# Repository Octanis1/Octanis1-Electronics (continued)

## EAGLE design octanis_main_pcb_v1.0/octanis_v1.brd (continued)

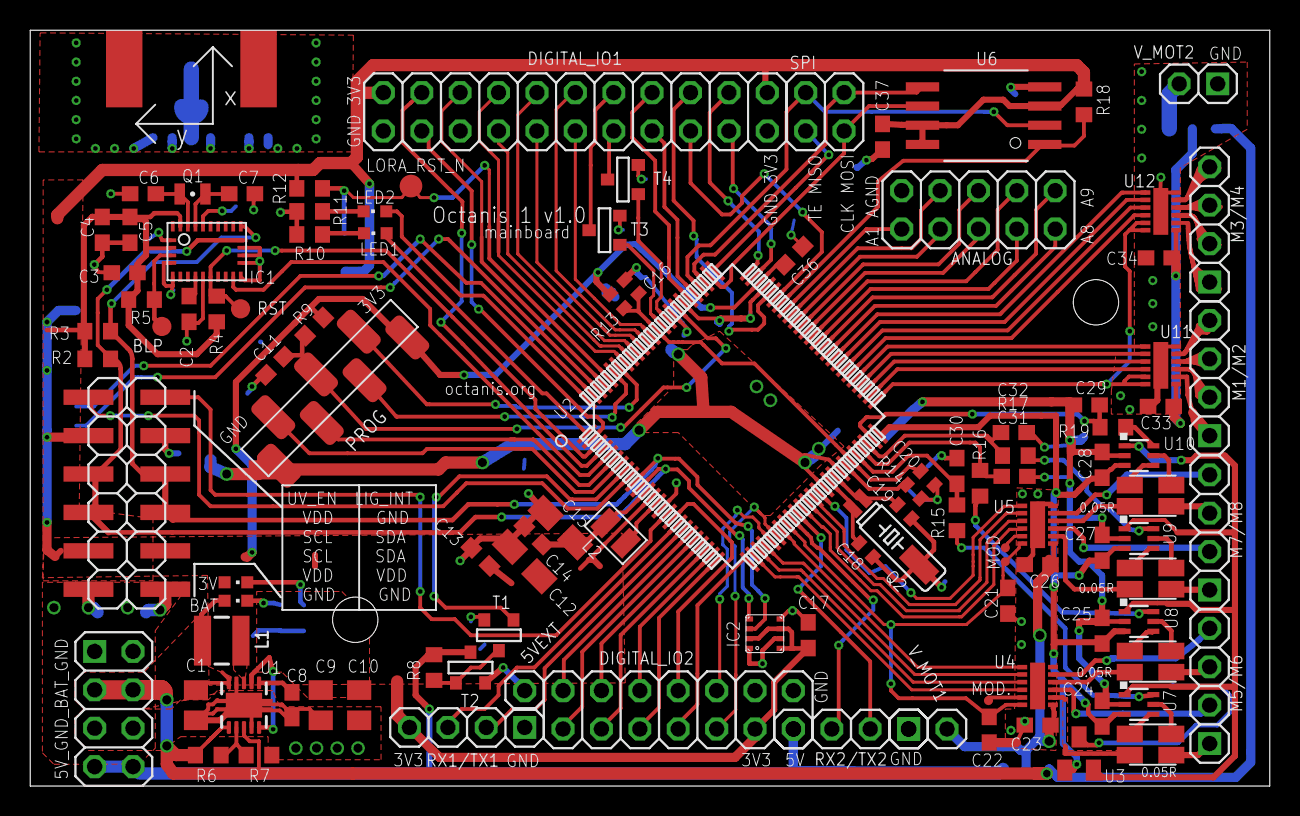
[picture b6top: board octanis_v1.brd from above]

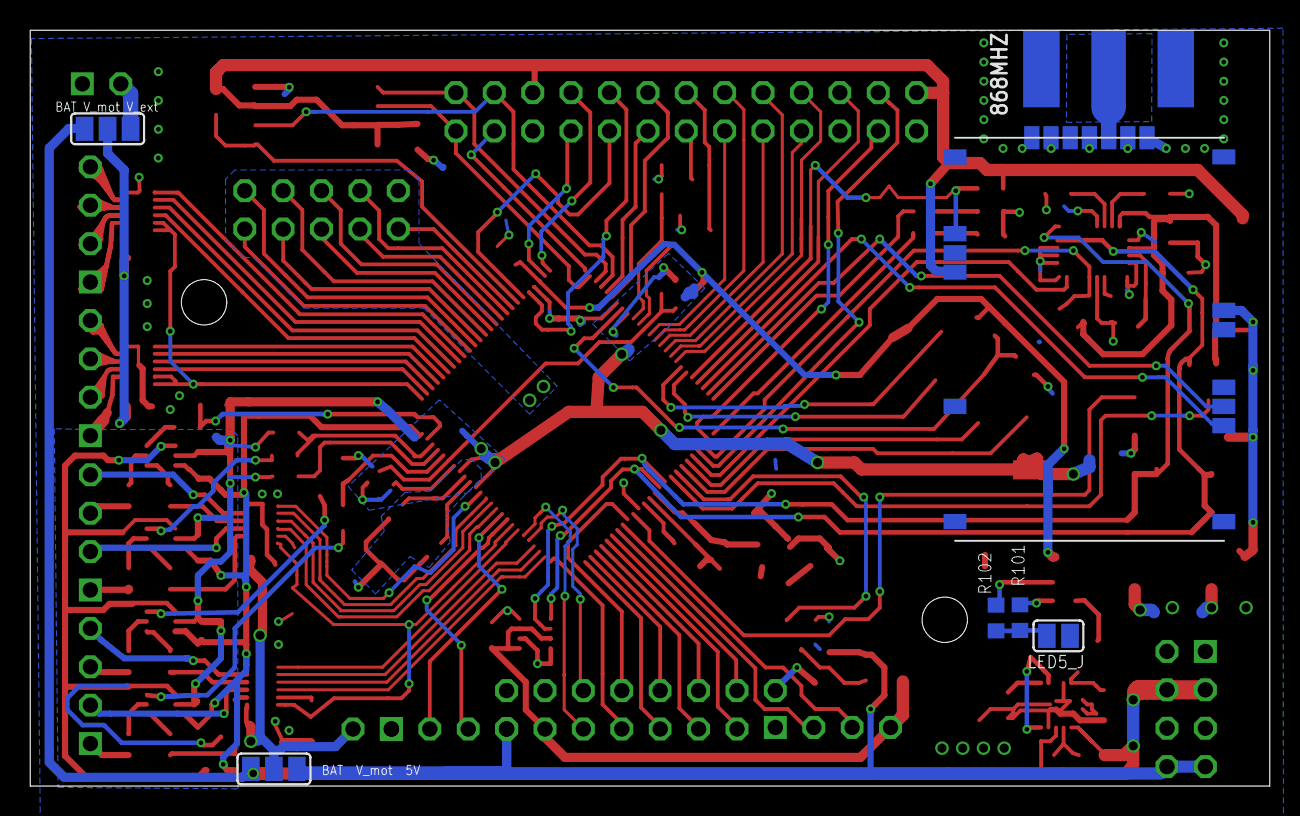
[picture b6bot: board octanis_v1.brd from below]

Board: 2 copper layers, 82.0 x 50.0 mm, 117 parts (7 on the bottom side), 151 nets.

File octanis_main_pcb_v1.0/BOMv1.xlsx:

Part | list exported from / | Users/raffael/Deskto | p/Octanis/Octanis1-El | ectronics/octa | nis_main_pcb_v1.0/octanis_v1.sch at | 42442.656944444447
Qty | Value | Device | Package | Parts |  | Description MF MPN OC_FARNELL OC_NEWARK PACKAGE SUPPLIER TP_SIGNAL_NAME URL VAL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
1 | 142-0701-801 | SMACONNECTOR_EDGE | SMA_EDGELAUNCH | 868MHZ |  | SMA Connector
4 | 0.05R | CURRENT_RESISTOR | 4PADS_RESISTOR | RS1, RS2, RS3, | RS4
1 | 0R | R-EU_R0402 | R0402 | R13 |  | RESISTOR, European symbol
3 | 100k | R-EU_R0603 | R0603 | R4, R5, R12 |  | RESISTOR, European symbol
2 | 100n | C-EUC0402 | C0402 | C16, C20 |  | CAPACITOR, European symbol
8 | 100n | C-EUC0603 | C0603 | C2, C3, C8, C1 | 3, C14, C17, C36, C37 | CAPACITOR, European symbol
1 | 100k | R-EU_R0603 | R0603 | R18 |  | RESISTOR, European symbol
4 | 10n | C-EUC0603 | C0603 | C24, C25, C27, | C28 | CAPACITOR, European symbol
3 | 10u | C-EUC0805K | C0805K | C1, C9, C10 |  | CAPACITOR, European symbol
2 | 10u | CPOL-EUA/3216-18R | A/3216-18R | C12, C15 |  | POLARIZED CAPACITOR, European symbol
2 | 120n | C-EUC0603 | C0603 | C4, C5 |  | CAPACITOR, European symbol
2 | 12p | C-EUC0402 | C0402 | C18, C19 |  | CAPACITOR, European symbol
2 | 12p | C-EUC0603 | C0603 | C6, C7 |  | CAPACITOR, European symbol
3 | 1M | R-EU_R0603 | R0603 | R6, R7, R8 |  | RESISTOR, European symbol
3 | 1k | R-EU_R0603 | R0603 | R10, R11, R102 |  | RESISTOR, European symbol
1 | 1n | C-EUC0603 | C0603 | C11 |  | CAPACITOR, European symbol
3 | 2N7002P,215 | NMOSSOT23 | SOT-23 | T1, T3, T4 |  | MOS FET unknown unknown
1 | 1.2k | R-EU_R0603 | R0603 | R101 |  | RESISTOR, European symbol
1 | ST2012SB32768H5 | FC-12M | FC-12M | Q1 |  | kHz RANGE CRYSTAL UNIT http://www.mouser.ch/ProductDetail/ECS/ECS-327-125-12-TR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
1 | AB26TRQ-32.768kHz-T | MS3V-T1R | MS3V-T1R | Q2
1 | HT-193UYG-5592 | LEDCHIPLED_0603 | CHIPLED_0603 | 3V |  | LED green
2 | 4.7k | R-EU_R0603 | R0603 | R2, R3 |  | RESISTOR, European symbol
1 | 4.7uH | LQM2MP_G0 | 806 | L2
10 | 470n | C-EUC0603 | C0603 | C21, C22, C23, | C26, C29, C30, C31, C32, C33, C34 | CAPACITOR, European symbol
1 | 47k | R-EU_R0603 | R0603 | R9 |  | RESISTOR, European symbol
4 | 6.8k | R-EU_R0603 | R0603 | R15, R16, R17, | R19 | RESISTOR, European symbol
1 | 91k 0.1% ±25 ppm/°C | R-EU_R0402 | R0402 | R14 |  | RESISTOR, European symbol
1 | HT-193UYG-5592 | LEDCHIPLED_0603 | CHIPLED_0603 | BAT |  | LED green
1 | BME280 | BME280 | BME280 | IC2 |  | DIGITAL HUMIDITY, PRESSURE AND TEMPERATURE SENSOR* Digital interface I²C (up to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
1 | BNO055A | BNO055A | BNO055 | IC1
1 | BNO055_COORDINATES | BNO055_COORDINATES | BNO055_COORDINATES | U$3
1 | DMP2066LSN | PMOSSOT23 | SOT-23 | T2 |  | MOS FET unknown unknown
2 | DRV8835DSSR | DRV8836DSSR | SON50P200X300X80-13N | U4, U5 |  | DUAL LOW VOLTAGE H-BRIDGE IC,SON-12 DRV8836DSSR 2115236 94T6066 SON-12 TEXAS IN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
2 | DRV8836DSSR | DRV8836DSSR | SON50P200X300X80-13N | U11, U12 |  | DUAL LOW VOLTAGE H-BRIDGE IC,SON-12 DRV8836DSSR 2115236 94T6066 SON-12 TEXAS IN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
4 | INA210 | INA213 | SC70-6 | U7, U8, U9, U1 | 0 | Voltage
1 | LS Q976-NR-1 | LEDCHIPLED_0603 | CHIPLED_0603 | LED2 |  | LED red (LED0)
1 | HT-193UYG-5592 | LEDCHIPLED_0603 | CHIPLED_0603 | LED1 |  | LED green (LED1)
1 | LPS3015 | LPS3015 | LPS3015 | L1 |  | Shielded Power Inductor
1 | MAX6001SOT-23 | MAX6001SOT-23 | MAX6001 | U3
1 | MSP432 | MSP432 | PZ100 | U2
1 | RN2483 | RN2483 | RN2483 | U100 |  | Microchip Low-Power Long Range LoRaTM Technology Transceiver Module RN2483
1 | S25FL127S | SST25VF064C | SOIC_8-LEAD | U6
1 | TPS61201 | TPS61201 | S-PDSO-N10 | U1 |  | LOW INPUT VOLTAGE SYNCHRONOUS BOOST CONVERTER WITH 1.3-A SWITCHES TPS61201DRCT 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
3 | TPTP06R | TPTP06R | TP06R | MOD, MOD., VCC | MOT | Test pad

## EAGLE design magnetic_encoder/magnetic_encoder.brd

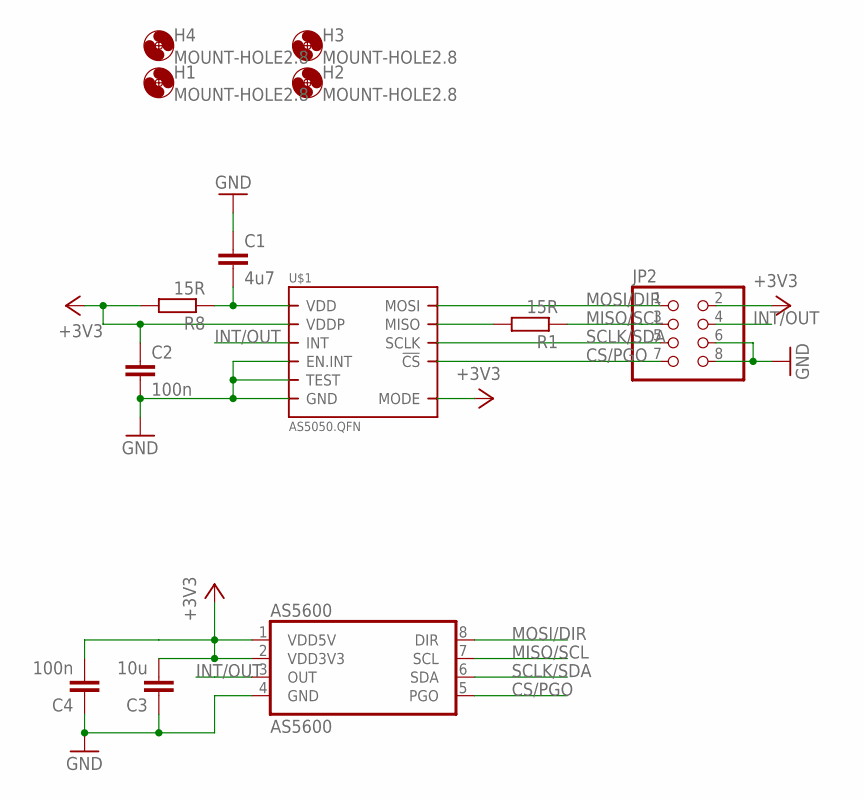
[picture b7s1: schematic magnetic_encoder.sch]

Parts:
AS5600: AS5600; SOIC-8
C1: 4u7; C0603
C2, C4: 100n; C0603
C3: 10u; C0603
H1, H2, H3, H4: MOUNT-HOLE2.8; 2,8
JP2: PINHD-2X4; 2X04
R1, R8: 15R; R0603
U$1: AS5050.QFN; QFN.16

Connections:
+3V3: AS5600.1 (VDD5V), AS5600.2 (VDD3V3), C2.1, C3.2, C4.2, JP2.2, R8.2, U$1.11 (VDDP), U$1.14 (MODE)
CS/PGO: AS5600.5 (PGO), JP2.7, U$1.4 (!CS)
GND: AS5600.4 (GND), C1.1, C2.2, C3.1, C4.1, JP2.6, JP2.8, U$1.9 (TEST), U$1.10 (EN.INT), U$1.13 (GND)
INT/OUT: AS5600.3 (OUT), JP2.4, U$1.15 (INT)
MISO/SCL: AS5600.7 (SCL), JP2.3, R1.1
MOSI/DIR: AS5600.8 (DIR), JP2.1, U$1.1 (MOSI)
unnamed: C1.2, R8.1, U$1.12 (VDD)
unnamed: R1.2, U$1.2 (MISO)
SCLK/SDA: AS5600.6 (SDA), JP2.5, U$1.3 (SCLK)

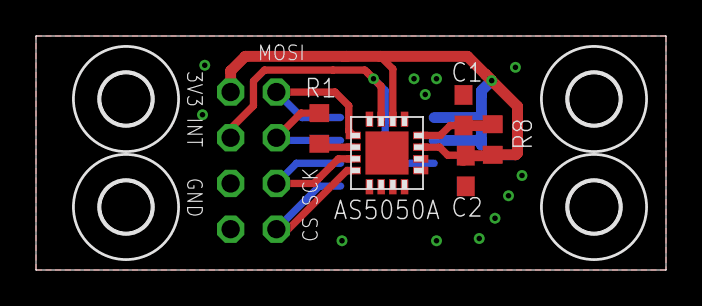
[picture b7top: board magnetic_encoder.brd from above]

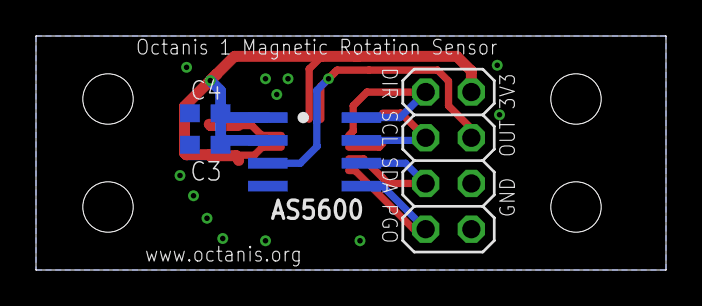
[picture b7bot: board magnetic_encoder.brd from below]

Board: 2 copper layers, 35.0 x 13.0 mm, 13 parts (4 on the bottom side), 9 nets.

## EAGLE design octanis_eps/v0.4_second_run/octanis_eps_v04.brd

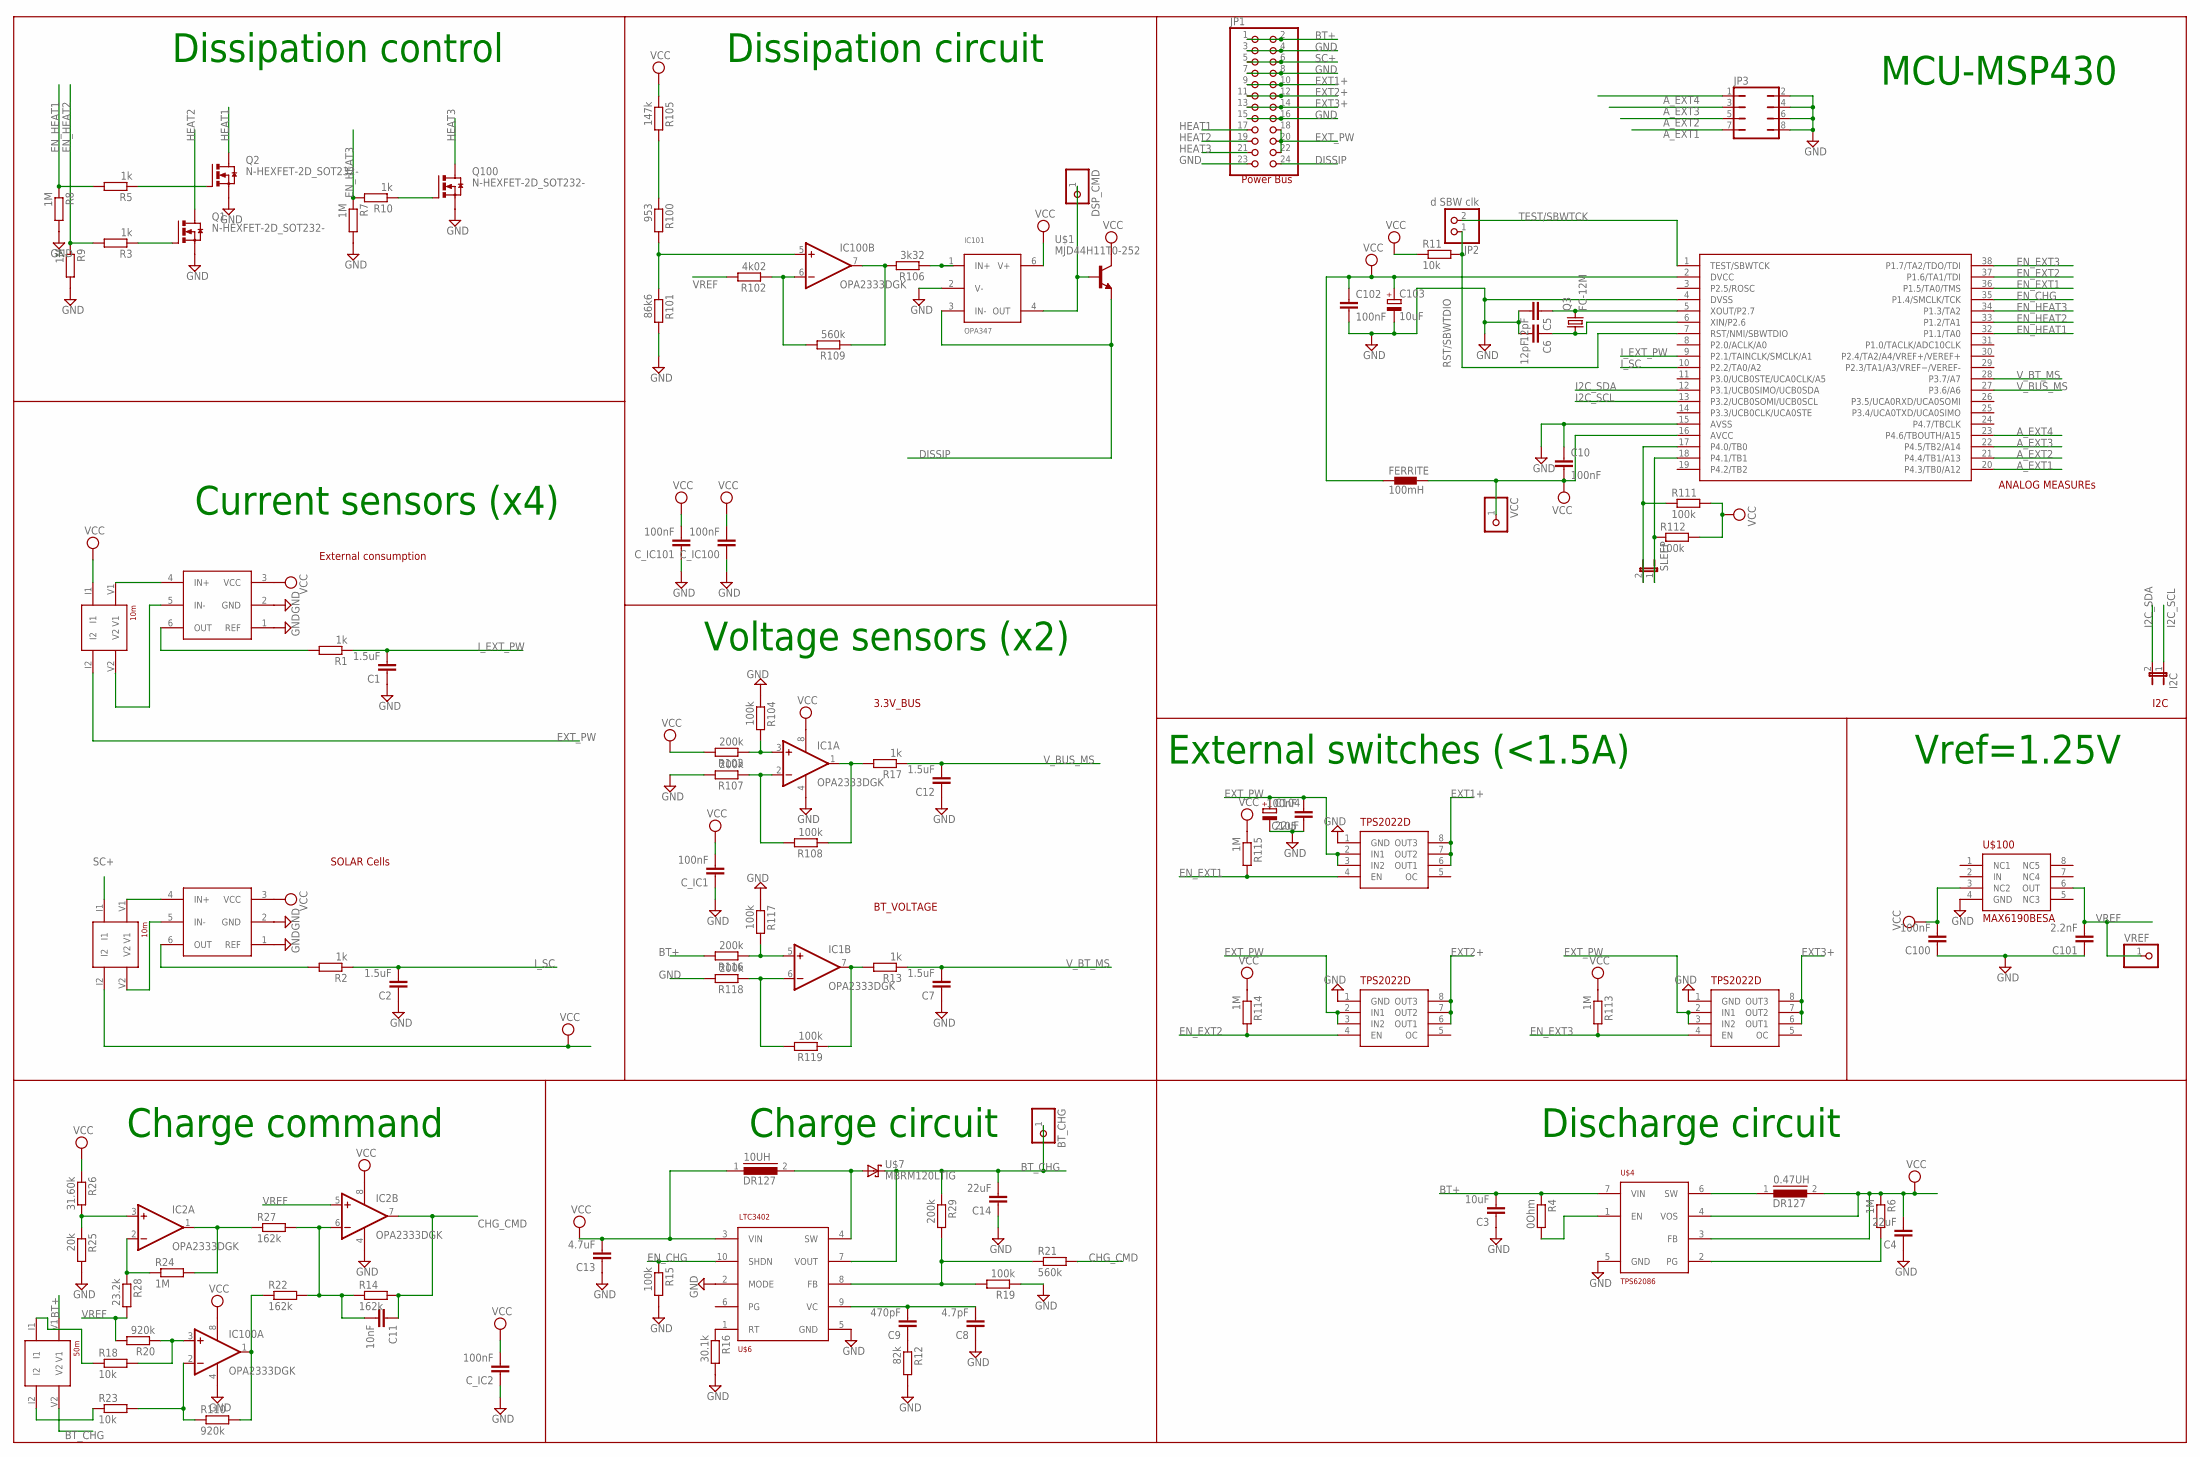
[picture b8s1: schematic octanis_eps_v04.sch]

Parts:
0.47UH, 10UH: DR127
BT_CHG: PINHD-1X1; 1X01
C1, C2, C7, C12: 1.5uF; C0603
C3: 10uF; C1206
C4: 22uF; C1206
C5, C6: 12pF; C0603
C8: 4.7pF; C0603
C9: 470pF; C0603
C10, C100, C102, C105: 100nF; C0603
C11: 10nF; C0603
C13: 4.7uF; C1206
C14: 22uF; C0603
C101: 2.2nF; C0603
C103: 10uF; A/3216-18R
C104: 22uF; A/3216-18R
C_IC1, C_IC2, C_IC100, C_IC101: 100nF; C0603
DSP_CMD: PINHD-1X1; 1X01
FERRITE: 100mH; 0402
I2C: JP1E; JP1
IC1, IC2, IC100: OPA2333DGK; MSOP08
IC101: OPA347; SC70-5
JP1: PINHD-2X12; 2X12
JP2: d SBW clk; 1X02
JP3: JP4Q
Q1, Q2, Q100: N-HEXFET-2D_SOT232-; SOT223
Q3: FC-12M
R1, R2, R3, R5, R10, R13, R17: 1k; R0603
R4: 0Ohm; R0603
R6, R7, R8, R9, R24, R113, R114, R115: 1M; R0603
R11, R18, R23: 10k; R0603
R12: 82k; R0603
R14, R22, R27: 162k; R0603
R15, R19, R104, R108, R111, R112, R117, R119: 100k; R0603
R16: 30.1k; R0603
R20, R110: 920k; R0603
R21, R109: 560k; R0603
R25: 20k; R0603
R26: 31.60k; R0603
R28: 23.2k; R0603
R29, R103, R107, R116, R118: 200k; R0603
R100: 953; R0603
R101: 86k6; R0603
R102: 4k02; R0603
R105: 147k; R0603
R106: 3k32; R0603
RSENSE1: 10m; 4PADS_RESISTOR
RSENSE2: 50m; 4PADS_RESISTOR
R_SENSE1: 10m; 4PADS_RESISTOR
SLEEP: JP1E; JP1
U$1: MJD44H11T0-252; TO252
U$2, U$3: INA213; SC70-6
U$4: TPS62086; QFN-7
U$5: MSP430G2544; TSSOP38_MSPGXX44_SERIES
U$6: LTC3402; MSOP10
U$7: MBRM120LTIG; DO216AA
U$100: MAX6190BESA; SO8
U$101, U$102, U$103: TPS2022D; SO8
VCC: PINHD-1X1; 1X01
VREF: PINHD-1X1; 1X01

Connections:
A_EXT1: JP3.7, U$5.20 (P4.3/TB0/A12)
A_EXT2: JP3.5, U$5.21 (P4.4/TB1/A13)
A_EXT3: JP3.3, U$5.22 (P4.5/TB2/A14)
A_EXT4: JP3.1, U$5.23 (P4.6/TBOUTH/A15)
BT+: C3.2, JP1.1, JP1.2, R4.1, R116.2, RSENSE2.V1, U$4.7 (VIN)
BT_CHG: BT_CHG.1, C14.2, R29.1, RSENSE2.V2, U$6.7 (VOUT), U$7.C (K)
CHG_CMD: C11.1, IC2.7 (OUT), R14.2, R21.2
DISSIP: IC101.3 (IN-), JP1.24, U$1.3 (E)
EN_CHG: R15.1, U$5.35 (P1.4/SMCLK/TCK), U$6.10 (SHDN)
EN_EXT1: R115.2, U$5.36 (P1.5/TA0/TMS), U$103.4 (EN)
EN_EXT2: R114.2, U$5.37 (P1.6/TA1/TDI), U$102.4 (EN)
EN_EXT3: R113.2, U$5.38 (P1.7/TA2/TDO/TDI), U$101.4 (EN)
EN_HEAT1: R5.2, R8.1, U$5.32 (P1.1/TA0)
EN_HEAT2: R3.2, R9.1, U$5.33 (P1.2/TA1)
EN_HEAT3: R7.1, R10.2, U$5.34 (P1.3/TA2)
EXT1+: JP1.9, JP1.10, U$103.6 (OUT1), U$103.7 (OUT2), U$103.8 (OUT3)
EXT2+: JP1.11, JP1.12, U$102.6 (OUT1), U$102.7 (OUT2), U$102.8 (OUT3)
EXT3+: JP1.13, JP1.14, U$101.6 (OUT1), U$101.7 (OUT2), U$101.8 (OUT3)
EXT_PW: C104.+, C105.2, JP1.18, JP1.20, JP1.22, R_SENSE1.I2, U$101.2 (IN1), U$101.3 (IN2), U$102.2 (IN1), U$102.3 (IN2), U$103.2 (IN1), U$103.3 (IN2)
GND: C1.1, C2.1, C3.1, C4.1, C5.2, C6.2, C7.1, C8.1, C10.1, C12.1, C13.1, C14.1, C100.1, C101.1, C102.2, C103.-, C104.-, C105.1, C_IC1.1, C_IC2.1, C_IC100.1, C_IC101.1, IC1.4 (V-), IC2.4 (V-), IC100.4 (V-), IC101.2 (V-), JP1.3, JP1.4, JP1.7, JP1.8, JP1.15, JP1.16, JP1.23, JP3.2, JP3.4, JP3.6, JP3.8, Q1.3 (S), Q2.3 (S), Q100.3 (S), R7.2, R8.2, R9.2, R12.2, R15.2, R16.2, R19.1, R25.2, R101.2, R104.1, R107.2, R117.1, R118.2, U$2.1 (REF), U$2.2 (GND), U$3.1 (REF), U$3.2 (GND), U$4.5 (GND), U$5.4 (DVSS), U$5.15 (AVSS), U$6.2 (MODE), U$6.5 (GND), U$100.4 (GND), U$101.1 (GND), U$102.1 (GND), U$103.1 (GND)
HEAT1: JP1.17, Q2.2 (D), Q2.4 (D)
HEAT2: JP1.19, Q1.2 (D), Q1.4 (D)
HEAT3: JP1.21, Q100.2 (D), Q100.4 (D)
I2C_SCL: I2C.1, U$5.13 (P3.2/UCB0SOMI/UCB0SCL)
I2C_SDA: I2C.2, U$5.12 (P3.1/UCB0SIMO/UCB0SDA)
I_EXT_PW: C1.2, R1.1, U$5.9 (P2.1/TAINCLK/SMCLK/A1)
I_SC: C2.2, R2.1, U$5.10 (P2.2/TA0/A2)
unnamed: R1.2, U$3.6 (OUT)
unnamed: R2.2, U$2.6 (OUT)
unnamed: R16.1, U$6.1 (RT)
unnamed: C9.1, R12.1
unnamed: IC100.1 (OUT), R22.1, R110.2
unnamed: IC2.3 (+IN), R25.1, R26.2
unnamed: IC2.2 (-IN), R24.1, R28.1
unnamed: C8.2, C9.2, U$6.9 (VC)
unnamed: IC2.1 (OUT), R24.2, R27.1
unnamed: IC1.7 (OUT), R13.2, R119.1
unnamed: C11.2, IC2.6 (-IN), R14.1, R22.2, R27.2
unnamed: IC1.1 (OUT), R17.2, R108.1
unnamed: IC1.2 (-IN), R107.1, R108.2
unnamed: IC1.3 (+IN), R103.1, R104.2
unnamed: IC1.6 (-IN), R118.1, R119.2
unnamed: IC1.5 (+IN), R116.1, R117.2
unnamed: IC100.2 (-IN), R23.2, R110.1
unnamed: R100.1, R105.2
unnamed: IC100.5 (+IN), R100.2, R101.1
unnamed: IC100.6 (-IN), R102.1, R109.2
unnamed: IC100.7 (OUT), R106.2, R109.1
unnamed: IC101.1 (IN+), R106.1
unnamed: R19.2, R21.1, R29.2, U$6.8 (FB)
unnamed: 10UH.2, U$6.4 (SW), U$7.A
unnamed: R6.2, U$4.2 (PG)
unnamed: 0.47UH.1, U$4.6 (SW)
unnamed: IC100.3 (+IN), R18.2, R20.1
unnamed: Q2.1 (G), R5.1
unnamed: R4.2, U$4.1 (EN)
unnamed: Q1.1 (G), R3.1
unnamed: R_SENSE1.V1, U$3.4 (IN+)
unnamed: R_SENSE1.V2, U$3.5 (IN-)
unnamed: RSENSE1.V1, U$2.4 (IN+)
unnamed: RSENSE1.V2, U$2.5 (IN-)
unnamed: Q100.1 (G), R10.1
unnamed: R23.1, RSENSE2.I2
unnamed: R18.1, RSENSE2.I1
unnamed: DSP_CMD.1, IC101.4 (OUT), U$1.1 (B)
unnamed: C5.1, Q3.2, U$5.5 (XOUT/P2.7)
unnamed: C6.1, Q3.1, U$5.6 (XIN/P2.6)
RST/SBWTDIO: JP2.1, R11.2, U$5.7 (RST/NMI/SBWTDIO)
SC+: JP1.5, JP1.6, RSENSE1.I1
TB0: R111.1, SLEEP.2, U$5.17 (P4.0/TB0)
TB1: R112.1, SLEEP.1, U$5.18 (P4.1/TB1)
TEST/SBWTCK: JP2.2, U$5.1 (TEST/SBWTCK)
VCC: 0.47UH.2, 10UH.1, C4.2, C10.2, C13.2, C100.2, C102.1, C103.+, C_IC1.2, C_IC2.2, C_IC100.2, C_IC101.2, FERRITE.1, FERRITE.2, IC1.8 (V+), IC2.8 (V+), IC100.8 (V+), IC101.6 (V+), R6.1, R11.1, R26.1, R103.2, R105.1, R111.2, R112.2, R113.1, R114.1, R115.1, RSENSE1.I2, R_SENSE1.I1, U$1.2 (C), U$2.3 (VCC), U$3.3 (VCC), U$4.3 (FB), U$4.4 (VOS), U$5.2 (DVCC), U$5.16 (AVCC), U$6.3 (VIN), U$100.3 (NC2), VCC.1
VREF: C101.2, IC2.5 (+IN), R20.2, R28.2, R102.2, U$100.6 (OUT), VREF.1
V_BT_MS: C7.2, R13.1, U$5.28 (P3.7/A7)
V_BUS_MS: C12.2, R17.1, U$5.27 (P3.6/A6)

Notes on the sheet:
Vref=1.25V
Current sensors (x4)
SOLAR Cells
3.3V_BUS
Charge circuit
Discharge circuit
External switches (<1.5A)
MCU-MSP430
Voltage sensors (x2)
BT_VOLTAGE
Dissipation circuit
ANALOG MEASUREs
I2C
External consumption
Dissipation control
Power Bus
Charge command

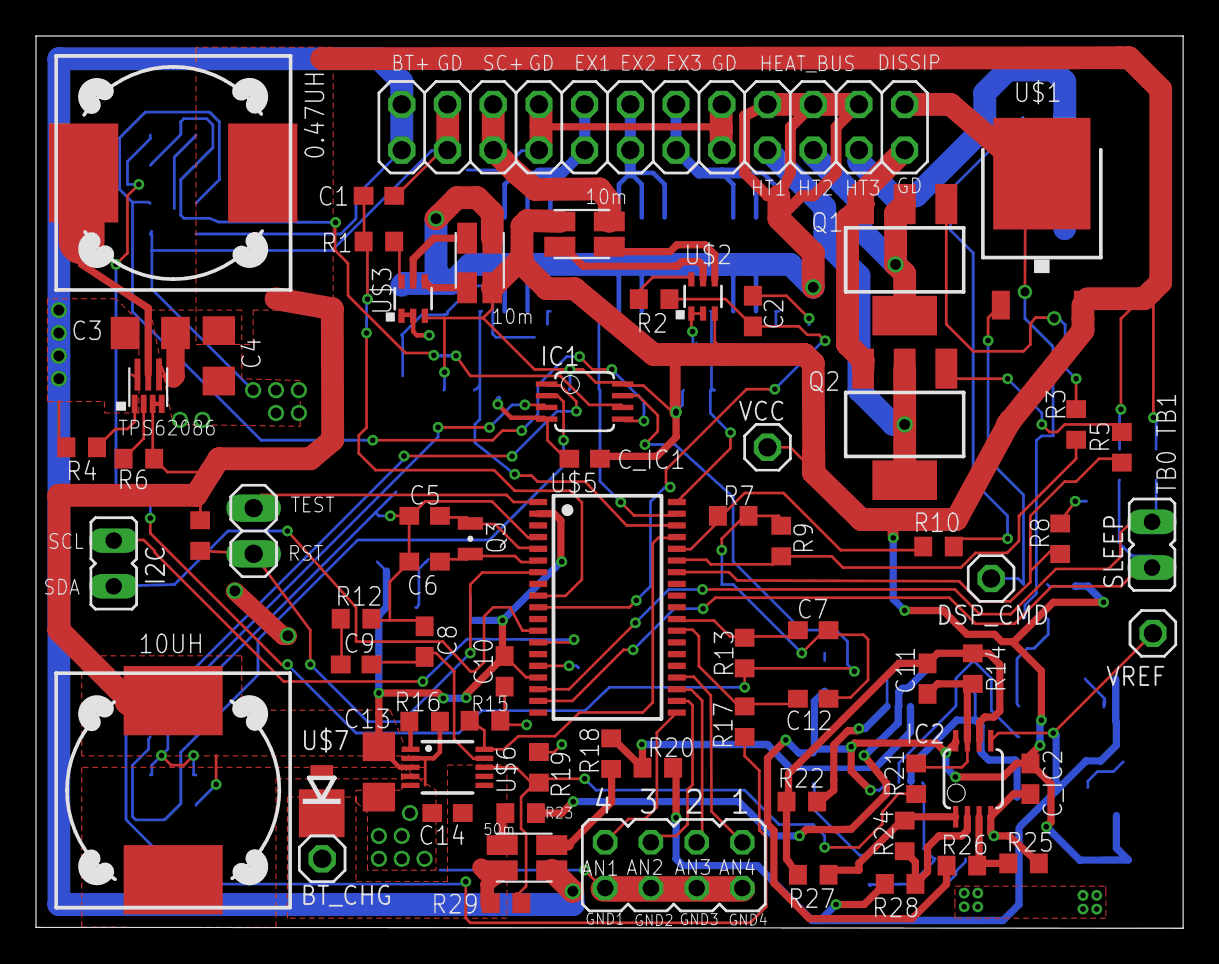
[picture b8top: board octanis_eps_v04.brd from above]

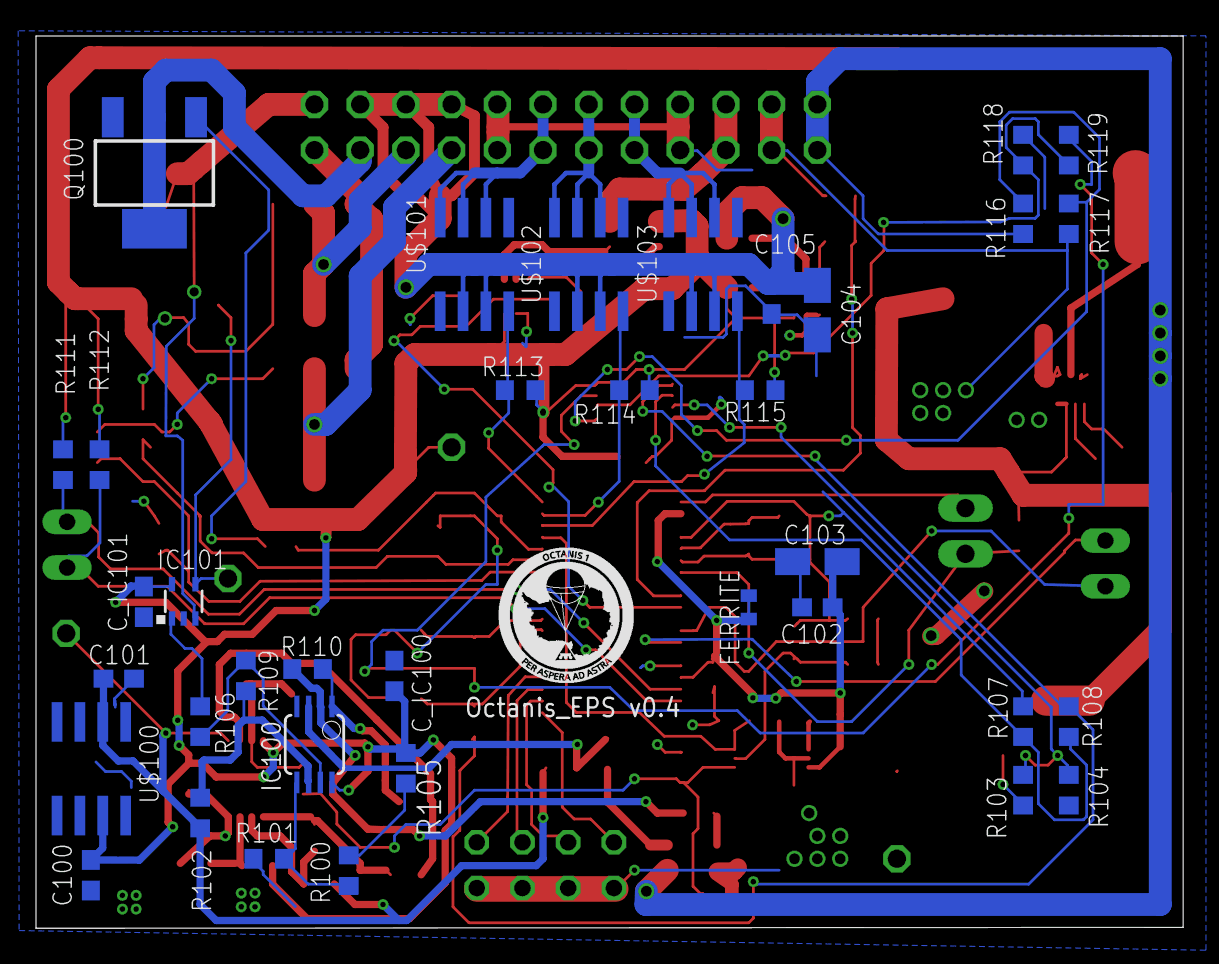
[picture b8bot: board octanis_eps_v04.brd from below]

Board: 4 copper layers, 63.7 x 49.6 mm, 107 parts (36 on the bottom side), 76 nets.

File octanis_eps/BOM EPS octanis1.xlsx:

BOM EPS Octanis1
Active components
Reference | Unit Price (CHF) | Qty | Total price | Manufacturer | Package | Provider | Description
TPS62086RLTT | 6.35 | 1 | 6.35 | TI | VQFN-7 | Farnell | 3.3V 3A buck converter (discharge)
LTC3402EMS#PBF | 11.1 | 1 | 11.1 | Linear Devices | MSOP10 | Farnell | Adjustable boost converter 2A (charge
MSP430G2744IDA38R | 2.85 | 1 | 2.85 | TI | TSSOP38 | TI | MCU
INA213AIDCKT | 1.7 | 2 | 3.4 | TI | SC70-6 | Farnell | Gain 50 current sensor 35µA polarization
TPS2022D | 3.5 | 3 | 10.5 | TI | SOIC8 | Farnell | 1.5A distribution switch
ADR127BUJZ-REEL7 | 10.15 | 1 | 10.15 | Analog Devices | TSOT23-6 | Farnell | Precision 1.25V voltage reference
OPA2333AIDGKT | 3.6 | 4 | 14.4 | TI | MSOP8 | Farnell | Low power OPA 2 channels
FDV301N | 3.7999999999999999E-2 | 3 | 0.11399999999999999 | Farichild | SOT-23 | Farnell | N canal MOSFET
IRLL024NPBF | 1.25 | 3 | 3.75 | IR | SOT-223 | Farnell | N hexfet 2V threshold
MJD44H11T4 | 0.71299999999999997 | 1 | 0.71299999999999997 | ST micro | TO-252 | Farnell | BJT
Reference | Unit Price (CHF) | Qty | Total price | Manufacturer | Package | Provider | Description
1kOhm | 1.4999999999999999E-2 | 3 | 4.4999999999999998E-2 | - | 603 | Farnell
50mOhm 0.1% | 0.1 | 3 | 0.30000000000000004 | - | 1206 | Farnell | current shunts precision resistor
10kOhm 0.1% | 0.03 | 6 | 0.18 | - | 603 | Farnell
100kOhm | 1.4999999999999999E-2 | 5 | 7.4999999999999997E-2 | - | 603 | Farnell
200kOhm | 1.4999999999999999E-2 | 5 | 7.4999999999999997E-2 | - | 603 | Farnell
147kOhm 0.1% | 0.03 | 1 | 0.03 | - | 603 | Farnell
953Ohm 0.1% | 0.03 | 1 | 0.03 | - | 603 | Farnell
86k6Ohm 0.1% | 0.5 | 1 | 0.5 | - | 603 | Farnell
4k02Ohm 0.1% | 0.5 | 1 | 0.5 | - | 603 | Farnell
560kOhm 0.1% | 0.1 | 2 | 0.2 | - | 603 | Farnell
3k32Ohm 0.1% | 0.5 | 1 | 0.5 | - | 603 | Farnell
30k1Ohm 0.1% | 0.5 | 1 | 0.5 | - | 603 | Farnell
1.3MOhm 0.1% | 0.5 | 1 | 0.5 | - | 603 | Farnell
549kOhm 0.1% | 0.5 | 1 | 0.5 | - | 603 | Farnell
82kOhm 0.1% | 0.5 | 1 | 0.5 | - | 603 | Farnell
1MOhm | 1.4999999999999999E-2 | 6 | 0.09 | - | 603 | Farnell
162kOhms 1% | 1.4999999999999999E-2 | 3 | 4.4999999999999998E-2 |  | 603 | Farnell
20kOhms 0.11% | 0.03 | 1 | 0.03 |  | 603 | Farnell
23.2kOhms 0.1% | 0.03 | 1 | 0.03 |  | 603 | Farnell
31.60kOhms 0.1% | 0.03 | 1 | 0.03 |  | 603 | Farnell
920kOhms 0.1% | 0.03 | 1 | 0.03 |  | 603 | Farnell
MBRM120LT1G | 0.9 | 3 | 2.7 | - | D0216AA | Farnell | shottky
150nF | 0.03 | 4 | 0.12 | - | 603 | Farnell
100nF | 0.03 | 10 | 0.3 | - | 603 | Farnell
10nF | 0.03 | 10 | 0.3 | - | 603 | Farnell
12pF 1% | 0.5 | 2 | 1 | - | 603 | Farnell
10uF | 0.5 | 1 | 0.5 | - | A/3216-18R | Farnell | polarized capacitor
22uF | 0.5 | 1 | 0.5 | - | A/3216-18R | Farnell | polarized capacitor
470pF | 3.0000000000000001E-3 | 1 | 3.0000000000000001E-3 | - | 603 | Farnell
4.7pF | 3.0000000000000001E-3 | 1 | 3.0000000000000001E-3 | - | 603 | Farnell
4.7uF | 0.5 | 1 | 0.5 | - | 1206 | Farnell | X5R or X7R family recommended
22uF | 0.5 | 2 | 1 | - | 603 | Farnell | X5R or X7R family recommended
10uF | 0.5 | 2 | 1 | - | 1206 | Farnell | X5R or X7R family recommended
10uH | 1.25 | 1 | 1.25 | Coiltronics | DR127 | Farnell | Power inductor 10uH
DR127-R47-R. | 1.2 | 1 | 1.2 | Coiltronics | DR128 | Farnell | Power inductor 0.47uH
32Mhz crystal | 0.5 | 1 | 0.5 | - | FC-12M | Farnell | Crystal
 |  | Total | 78.893000000000001

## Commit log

2014-06-19 Adding solar charger / battery gauge dev board based on TI BQ24210 and TI BQ27510-G3. Samples ordered, dev board needs to be completed and ordered.
2014-06-19 Adding gitignore
2014-07-14 Drew Schematic for Battery Charger. Arranged parts on PCB.
2014-07-14 Completed Routing for Battery charging Part
2014-07-14 Added the correct MSP430 microcontroller with example circuit from LaunchPad DevBrd
2014-07-15 Added I2C
2014-07-15 Added Fuel Gauge Circuit in Schematic
2014-07-16 Renamed and placed Parts for fuel gauge part of circuit
2014-07-16 Rearranged some components and routes and increased thickness of power lines
2014-07-16 Calculated R-values for Battery chargin circuit
2014-07-22 changed PCB-size and Added 5V-booster circuit
2014-07-29 added heating circuit
2014-08-04 added heating circuit. added correct step up converter. rearranged components to top layer. drew bigger power traces.
2014-08-04 added H-bridge library
2014-08-05 arranged power components and h-bridges
2014-08-05 rearranged and routed fuel gauge circuit part
2014-08-05 connected h-bridges to pins
2014-08-05 h-bridge: connected sleep pin with mode pin
2014-08-06 deleted unnecessary components from launchpad board. rearranged
2014-08-06 mapped ports for motors
2014-08-06 routed motor ports
2014-08-06 added gyro, accelerometer, pressure sensor, compass, serial connectors, analog input pins.
2014-08-06 created gerber files, with logo. In v0.1
2014-08-06 corrected silk layer
2014-08-07 increased space between traces, connected ch_en and 5Ven to uC
2014-08-10 next version 0.2, bigger pcb, added humidity sensor
2015-01-22 octanis_eps first proto in progress
2015-01-22 replaced the msp430 to the same component like in the octanis 0.1 board
2015-01-22 eps board save Thu-22-01-2015
2015-01-28 initial prototype v0.1 of EPS PCB ready for production, BOM in process
2015-01-30 modified compact version schematics
2015-01-30 corrected zener connection error
2015-01-31 compact version 5X6cm with MSP420Gxx24
2015-02-02 completed documentation & added BOM
2015-02-10 correction & redesign on of the boost converter running
2015-02-10 completed FeedBack loop regulation on charge circuit & routing
2015-02-13 most recent version
2015-02-17 EPS revized, routing correction performed, voltage check point added, VCC corrected
2015-02-18 added pull down on heat EN entries
2015-02-18 added 0Ohm jumper on discharge circuit
2015-02-21 generated Gerbers for EPS, cosmetic corrections
2015-02-23 added octanis logo and reorganised files
2015-02-23 modified BOM for EPS
2015-03-28 startet new mainboard PCB
2015-04-01 added aria bob
2015-04-01 changed to throughhole
2015-04-01 revoked changes
2015-04-01 with new library
2015-04-01 usb wires longer, ground plane, vdd trace wider
2015-04-05 starting layout v0.3
2015-04-05 layout done
2015-04-05 generated gerber
2015-04-05 SD card footprint aria bob
2015-04-05 changed board size, increased isolation of gnd
2015-04-06 replaced sensirion humidity sensor with bosch
2015-04-06 added holes
2015-04-08 layouting 0.4
2015-04-09 layout 0.4 almost done
2015-04-10 v0.4 layout finished
2015-04-11 gerber v0.4
2015-04-13 finished weather strip
2015-05-15 corrected I2C SDA short to 3V
2015-05-29 corrected footprints for MSP & Step down, 50mOhms still to be changed (4points probe)
2015-05-29 corrected MSP & Step-down foorptints, 50Ohms still to be changed (4points probe-type)
2015-05-29 reorganized folder and backed up files after bad merger operation
2015-05-29 new gerbers, carefull 4 point probes not ready yet
2015-07-26 pull-up on RST, need to modify the current sensor pads
2015-07-29 started mainboard v0.5 (added bosch accelerometer/gyro)
2015-07-29 various corrections on EPS v0.3, new v0.4 for second run
2015-07-31 rearranged GPIOs
2015-07-31 separated motor supply. added pull ups for sleep pin
2015-07-31 redesigned hx1 pins
2015-08-04 thicker analog tracks for CHGCMD, better analog Grounding (same ref), regenerated gerbers. Checked with Beat
2015-08-11 assigned all GPIO
2015-08-11 mainboard: digital gpio routed
2015-08-11 mainboard routing finished
2015-08-12 mainboard finished
2015-08-13 corrected UV sensor footprint
2015-08-13 modified silk screen for EPS
2015-08-15 added RST pull-up
2015-08-21 added current sensors to motors on mainboard
2015-08-21 silkscreen ready
2015-08-21 added Vref and low pass filters for current sensors to mainboard
2015-08-21 finised revised mainboard
2015-08-21 finished revised weather strip
2015-08-21 renumbered parts in mainboard
2015-08-24 added RN2483 LoRa module, separated 3v supply for motors and 5V converter from main circuit supply. *
2015-08-25 finished mainboard v0.5 silkscreen
2015-08-27 minor changes on mainboard
2015-08-28 added pull down on boost Cvtr enable pin, C1 and R34 in parallel, Note that Rsense = 10 mOhms instead of 50mOhms at the entry of the INA213 current sensors, Rsense 3 still at 50mOhms
2015-08-28 changed ADR127 1.25V ref for MAX6190BESA (lower power), added 2 pins with pull down for main board sleep, DRC checked. One OPA2333 need to be changed on disispation circuit.
2015-08-28 changed IC9A=OPA2333 (2ch) for IC9=0PA347 with SC70-5 small outline package. OPA347 allows for bigger driving currents so to be able to drive the POWER N-FET on disispation CMD (cf bgeissma for detai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
2015-08-29 re-routed EPS. adapted silkscreen on EPS
2015-08-31 generated gerber files and pannelized pcbs
2015-09-01 created bom for v0.5
2015-11-14 started v0.6 mainboard. moved motor drivers to the side
2015-11-15 finalized changes for v0.6. coax connector missing
2015-11-18 added SMA connector for LoRa
2015-11-19 DRC clean layout
2015-11-19 revised silklayer
2015-11-19 created gerber
2015-11-30 Spectrometer and LED-BOB added
    Added s2000 spectrometer interface and small LED-board
2015-11-30 First ideas of new EPS
2015-11-30 Added components for MPPT-charger
2015-12-10 adding Beat new EPS architecture schematics
2015-12-20 Arranged parts for EPS v05
2015-12-21 started manual routing
2015-12-27 Routed 3.3V, 5V and Solar Cell stepdown
2015-12-28 EPS v05 routed, except enable and GND
2015-12-28 Routed EPS v05, issue with heatpad under Solar and 5V DCDC
2015-12-29 EPS v05 routing complete
2015-12-30 Added mounting holes and header names
2015-12-30 magnetic encoder board
2015-12-30 silk layer
2016-01-02 minor eps changes. stencil laser cut files for v0.6 added
2016-01-03 Labels of EPS05 changed
2016-01-03 measured correct dimensions
2016-01-03 corrected eps libraries so that they are GERBER-izable. (ERROR was: 'Board contains a polygon that may cause extremely large plot data' and is due to drawn polygons with width=0 in tStop, tCream and 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
2016-01-03 pannelized EPS with magnet sensor board, created gerber files
2016-02-22 Started redesign of EPS
2016-02-24 started v1.0
2016-03-02 started v1.0 mainboard
2016-03-02 added 5V on-off switch and battery boost converter to mainboard
2016-03-02 silkscreen artwork, lightning input interrupt
2016-03-02 octanis 1.0 finished
2016-03-03 weather strip v3. revised mainboard v1
2016-03-03 created final gerber files
2016-03-05 replaced 3.3v converters to the BGA component. started moving components to make space on top side
2016-03-08 replaced MSP430 for more efficient model. added mosfet circuit braker to schematic
2016-03-08 restored old v0.5, renamed v1.0 correctly
2016-03-20 now all EPS components are on top side
2016-03-20 finished component placement of new EPS
2016-03-21 dru check; added proper grounding and AVCC for all amps
2016-03-21 removed ground loops
2016-03-21 reworked silkscreen
2016-03-21 final silk and minor copper rework. files ready for production
2016-03-23 removed stitching at 12V boost; final files that were sent to production
2016-04-05 corrected the feedback pin error on battery DC-DC converter.
2016-05-22 adjusted final resistor values for eps v1.0
2016-05-28 connected VCC of BMP280 to 3V3 -> v3.1
2016-06-11 Added direct battery out, 5V and USB charger
2016-06-21 EPS v2.0 finished routing
2016-06-21 performed DRC
2016-06-22 corrected some GND mistakes; finished v2.0 silk layer
2016-06-22 updated titles and moved logo
2016-06-23 finalized silkscreen, generated Gerber files for EPS v2; replaced UV sensor in weather board, generated gerber files for v4
